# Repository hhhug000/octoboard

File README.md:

# Octoboard

An ATmega328P-PU development board designed from scratch in KiCad for prototyping AVR projects without breadboard mess. It uses only THT components to simplify soldering, and does not use an onboard serial chip to save on cost and simplicity

Octoboard breaks out all the GPIO from the chip, and provides all power management and supporting hardware.

The BOM is for 5 boards, as that is the minimum I can buy from JLCPCB and some parts

Built for the Hack Club Stardance YSWS program

---

## Visuals

### Renders

| Front | Back | Angle |
| ----  | ---- | ----- |
|  |  |  |

### PCB

| All Layers | Front Layer | Back Layer |
| ---------- | ----------- | ---------- |
|  |  |  |

### Explainer Video

---

## Design and Specs

*   **Microcontroller** ATmega328P-PU (DIP-28 package)
*   **Clock speed** External 16 MHz crystal oscillator
*   **I/O** All GPIO pins broken out to standardized 2.54mm pitch female headers
*   **Power management** Steps down barrel jack or input voltage to clean filtered 5v for the chip, and broken out for components
*   **Programming** Is programmed with standard Arduino C++, or any other lang with support like TinyGo or Micropython

---

## Notes

Make sure to flash the bootloader to the board in Arduino IDE even if you will only use ICSP.
This is because it programs the fuses, and programs will not work properly without it.

---

## Programming

The device can be programmed in a variety of languages.
I have personally tested it with Arduino C++ and my own blockly based system.
The device can be programmed with avrdude or the arduino ide.

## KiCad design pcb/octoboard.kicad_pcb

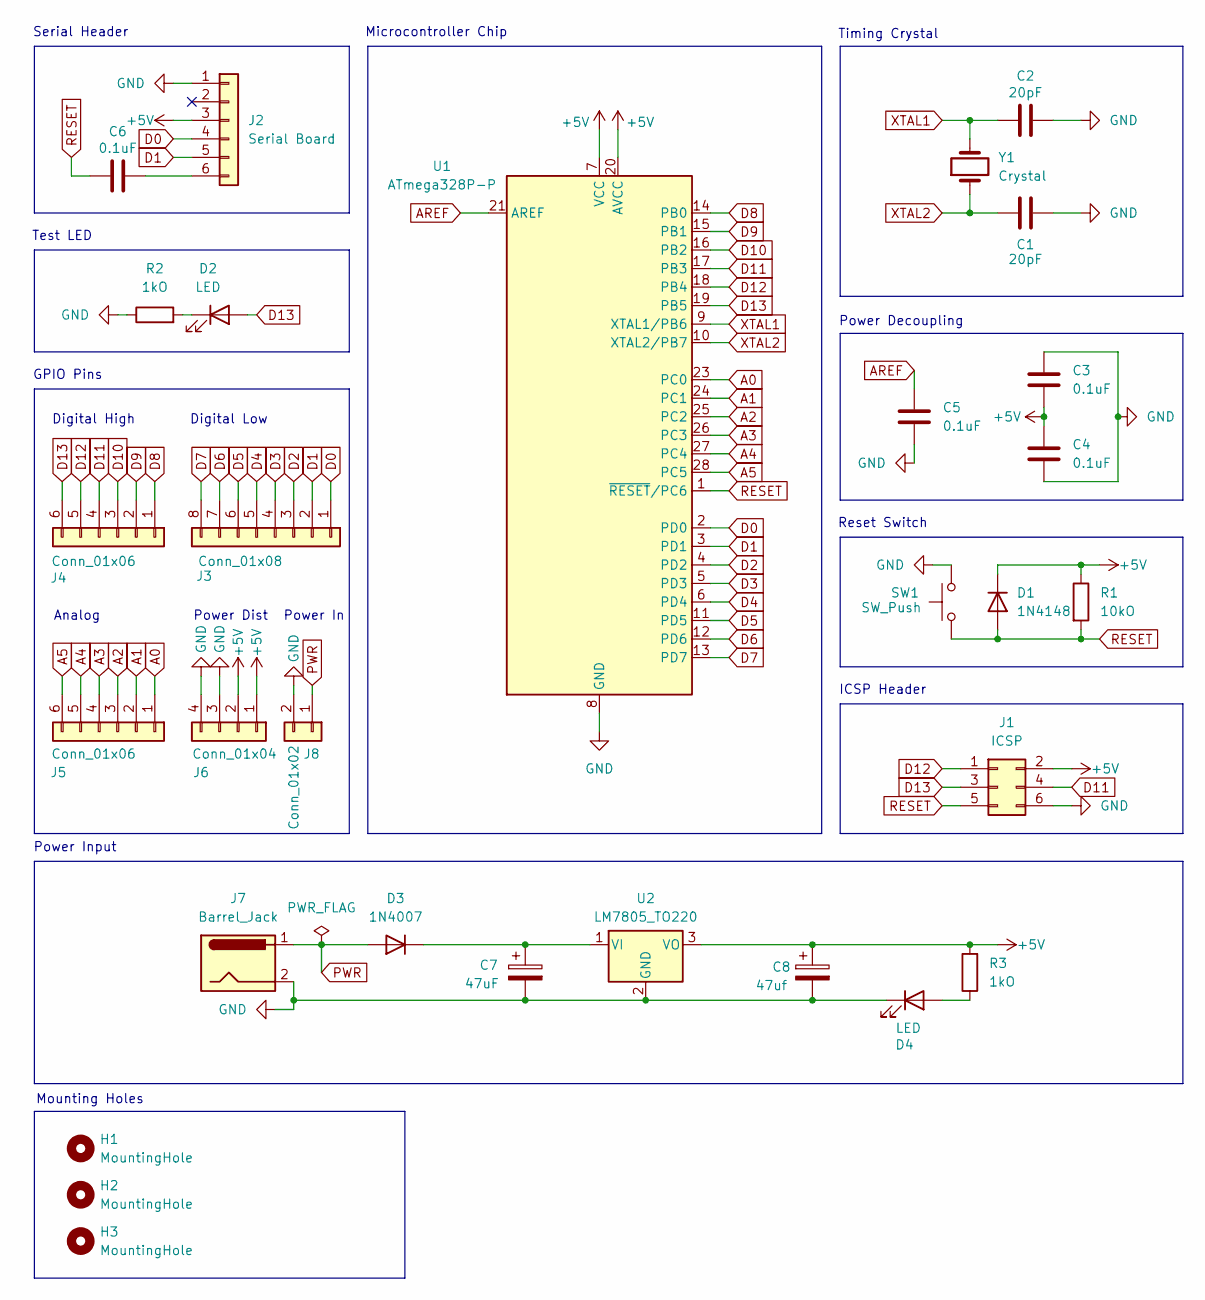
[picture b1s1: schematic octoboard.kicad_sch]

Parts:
C1, C2: 20pF; C_Disc_D3.8mm_W2.6mm_P2.50mm
C3, C4, C5, C6: 0.1uF; C_Disc_D5.0mm_W2.5mm_P2.50mm
C7: 47uF; CP_Radial_D5.0mm_P2.00mm
C8: 47uf; CP_Radial_D5.0mm_P2.00mm
D1: 1N4148; D_DO-35_SOD27_P7.62mm_Horizontal
D2, D4: LED; LED_D3.0mm
D3: 1N4007; D_DO-41_SOD81_P10.16mm_Horizontal
H1, H2, H3: MountingHole; MountingHole_2.2mm_M2
J1: ICSP; PinHeader_2x03_P2.54mm_Vertical
J2: Serial Board; PinHeader_1x06_P2.54mm_Vertical
J3: Conn_01x08; PinHeader_1x08_P2.54mm_Vertical
J4, J5: Conn_01x06; PinHeader_1x06_P2.54mm_Vertical
J6: Conn_01x04; PinHeader_1x04_P2.54mm_Vertical
J7: Barrel_Jack; BarrelJack_Horizontal
J8: Conn_01x02; PinHeader_1x02_P2.54mm_Vertical
R1: 10kO; R_Axial_DIN0207_L6.3mm_D2.5mm_P7.62mm_Horizontal
R2, R3: 1kO; R_Axial_DIN0207_L6.3mm_D2.5mm_P7.62mm_Horizontal
SW1: SW_Push; SW_PUSH_6mm
U1: ATmega328P-P; DIP-28_W7.62mm
U2: LM7805_TO220; TO-220-3_Vertical
Y1: Crystal; Crystal_HC49-4H_Vertical

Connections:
+5V: C3.2, C4.1, C8.1, D1.1 (K), J1.2, J2.3, J6.1, J6.2, R1.1, R3.2, U1.7 (VCC), U1.20 (AVCC), U2.3 (VO)
A0: J5.1, U1.23 (PC0)
A1: J5.2, U1.24 (PC1)
A2: J5.3, U1.25 (PC2)
A3: J5.4, U1.26 (PC3)
A4: J5.5, U1.27 (PC4)
A5: J5.6, U1.28 (PC5)
AREF: C5.1, U1.21 (AREF)
D0: J2.4, J3.1, U1.2 (PD0)
D1: J2.5, J3.2, U1.3 (PD1)
D2: J3.3, U1.4 (PD2)
D3: J3.4, U1.5 (PD3)
D4: J3.5, U1.6 (PD4)
D5: J3.6, U1.11 (PD5)
D6: J3.7, U1.12 (PD6)
D7: J3.8, U1.13 (PD7)
D8: J4.1, U1.14 (PB0)
D9: J4.2, U1.15 (PB1)
D10: J4.3, U1.16 (PB2)
D11: J1.4, J4.4, U1.17 (PB3)
D12: J1.1, J4.5, U1.18 (PB4)
D13: D2.2 (A), J1.3, J4.6, U1.19 (PB5)
GND: C1.1, C2.1, C3.1, C4.2, C5.2, C7.2, C8.2, D4.1 (K), J1.6, J2.1, J6.3, J6.4, J7.2, J8.2, R2.1, SW1.2, U1.8 (GND), U1.22 (GND), U2.2 (GND)
unnamed: D2.1 (K), R2.2
unnamed: C7.1, D3.1 (K), U2.1 (VI)
unnamed: D4.2 (A), R3.1
unnamed: C6.2, J2.6
PWR: D3.2 (A), J7.1, J8.1
RESET: C6.1, D1.2 (A), J1.5, R1.2, SW1.1, U1.1 (~RESET/PC6)
XTAL1: C2.2, U1.9 (XTAL1/PB6), Y1.2
XTAL2: C1.2, U1.10 (XTAL2/PB7), Y1.1

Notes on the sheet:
Serial Header
Power Input
Digital Low
Mounting Holes
Test LED
GPIO Pins
Power Dist
Timing Crystal
Power In
Microcontroller Chip
ICSP Header
Digital High
Analog
Reset Switch
Power Decoupling

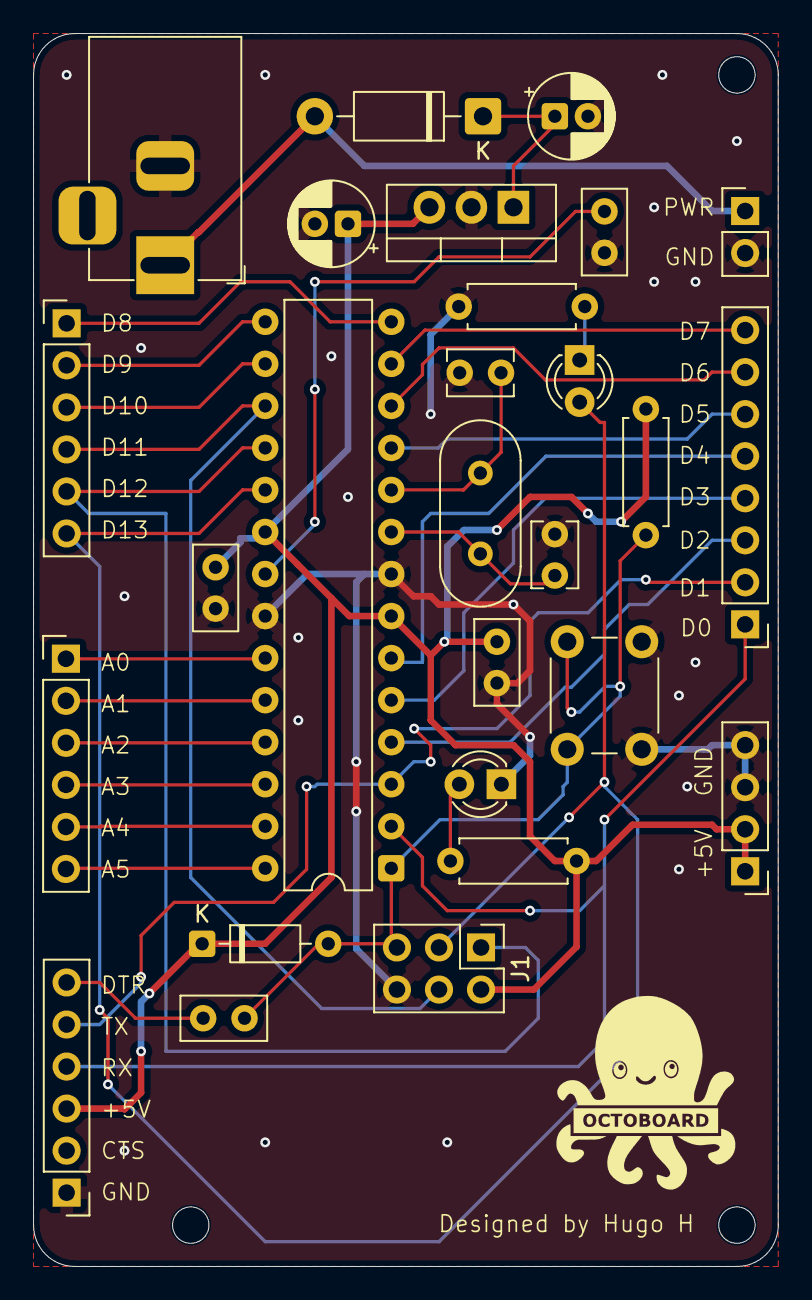
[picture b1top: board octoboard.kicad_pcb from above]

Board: 2 copper layers, 45.0 x 74.5 mm, 30 parts (0 on the bottom side), 31 nets.
